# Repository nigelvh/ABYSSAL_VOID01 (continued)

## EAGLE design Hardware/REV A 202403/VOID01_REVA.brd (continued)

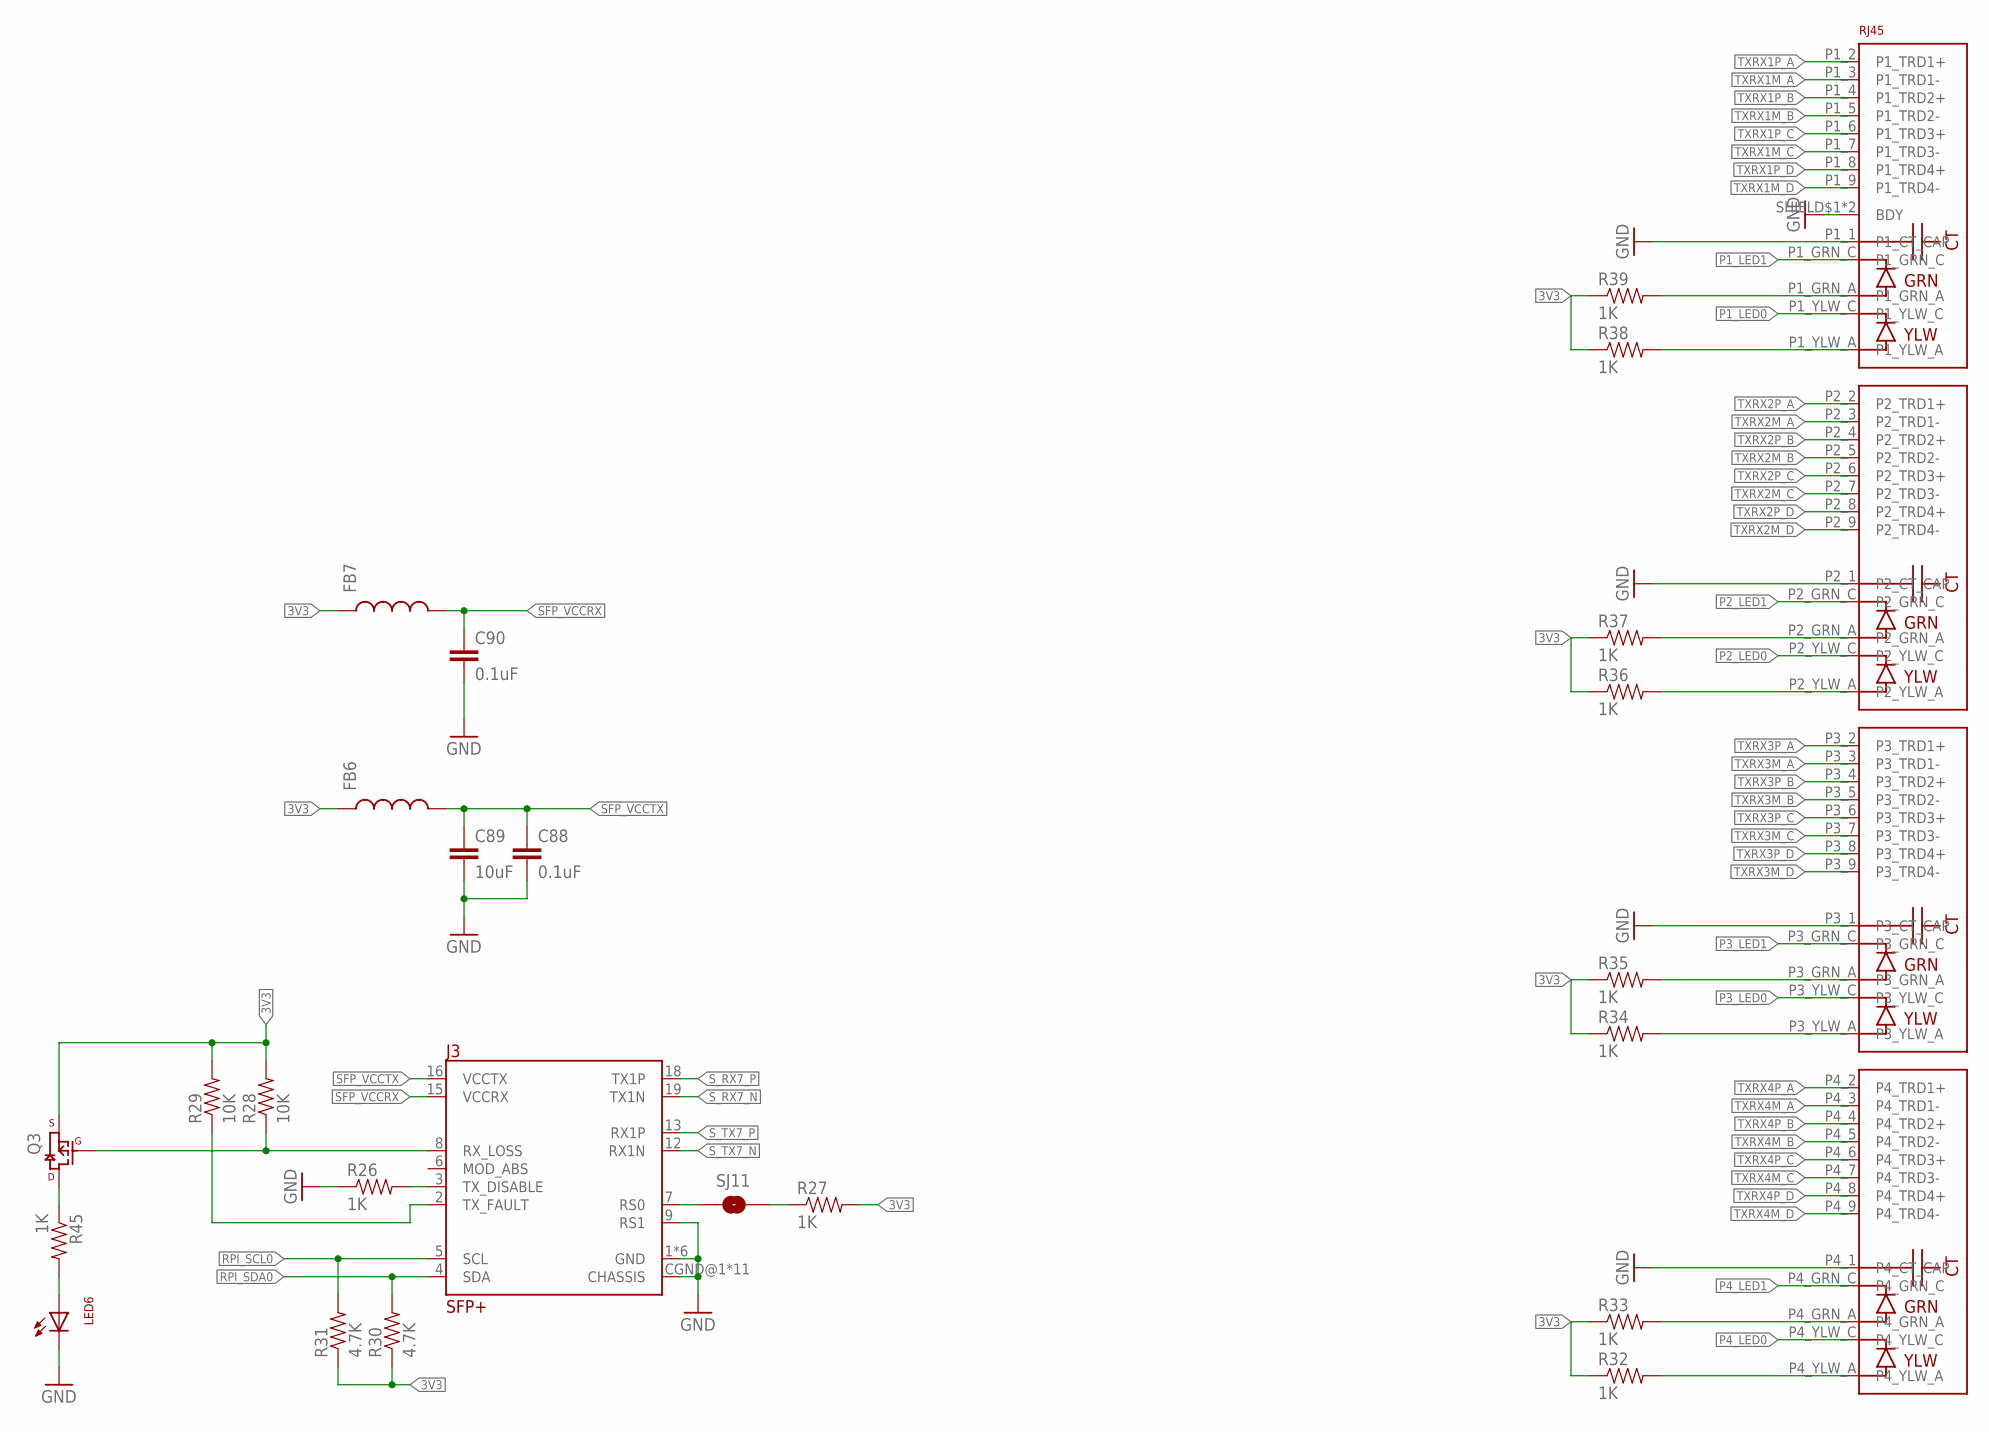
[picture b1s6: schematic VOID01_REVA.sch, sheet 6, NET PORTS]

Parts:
C88, C90: 0.1uF; 0402-CAP
C89: 10uF; 1206
FB6, FB7: INDUCTOR0805; 0805
J3: SFP; SFP_SOCKET_CAGE
J4: JXD0-4015NL
LED6: LED; LED_QBL7XX80D-MP4A
Q3: MOSFET_P_CHANNELAO3423; SOT-23
R26, R27: 1K; 0402-RES
R28: 10K; 0603-RES
R29: 10K; 0402-RES
R30, R31: 4.7K; 0402-RES
R32, R33, R34, R35, R36, R37, R38, R39, R45: 1K; 0603-RES
SJ11: SOLDERJUMPERNO; SJ_2S-NO

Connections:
3V3: FB6.1, FB7.1, Q3.2 (S), R27.2, R28.2, R29.2, R30.1, R31.1, R32.1, R33.1, R34.1, R35.1, R36.1, R37.1, R38.1, R39.1; also elsewhere on the board
GND: C88.2, C89.2, C90.2, J3.1 (GND), J3.9 (RS1), J3.10 (GND), J3.11 (GND), J3.14 (GND), J3.17 (GND), J3.20 (GND), J3.CGND@1 (CHASSIS), J3.CGND@6 (CHASSIS), J3.CGND@9 (CHASSIS), J3.CGND@11 (CHASSIS), J3.CGND@12 (CHASSIS), J3.CGND@13 (CHASSIS), J3.CGND@14 (CHASSIS), J3.CGND@15 (CHASSIS), J3.CGND@16 (CHASSIS), J3.CGND@19 (CHASSIS), J3.CGND@20 (CHASSIS), J4.P1_1 (P1_CT_CAP), J4.P2_1 (P2_CT_CAP), J4.P3_1 (P3_CT_CAP), J4.P4_1 (P4_CT_CAP), J4.SHIELD$1 (BDY), J4.SHIELD$5 (BDY), LED6.C, R26.1; also elsewhere on the board
unnamed: J4.P4_YLW_A, R32.2
unnamed: J4.P4_GRN_A, R33.2
unnamed: J4.P3_GRN_A, R35.2
unnamed: J4.P3_YLW_A, R34.2
unnamed: J4.P2_GRN_A, R37.2
unnamed: J4.P2_YLW_A, R36.2
unnamed: J4.P1_GRN_A, R39.2
unnamed: J4.P1_YLW_A, R38.2
unnamed: J3.3 (TX_DISABLE), R26.2
unnamed: J3.7 (RS0), SJ11.1
unnamed: R27.1, SJ11.2
unnamed: J3.8 (RX_LOSS), Q3.1 (G), R28.1
unnamed: J3.2 (TX_FAULT), R29.1
unnamed: LED6.A, R45.2
unnamed: Q3.3 (D), R45.1
P1_LED0: J4.P1_YLW_C; also elsewhere on the board
P1_LED1: J4.P1_GRN_C; also elsewhere on the board
P2_LED0: J4.P2_YLW_C; also elsewhere on the board
P2_LED1: J4.P2_GRN_C; also elsewhere on the board
P3_LED0: J4.P3_YLW_C; also elsewhere on the board
P3_LED1: J4.P3_GRN_C; also elsewhere on the board
P4_LED0: J4.P4_YLW_C; also elsewhere on the board
P4_LED1: J4.P4_GRN_C; also elsewhere on the board
RPI_SCL0: J3.5 (SCL), R31.2; also elsewhere on the board
RPI_SDA0: J3.4 (SDA), R30.2; also elsewhere on the board
SFP_VCCRX: C90.1, FB7.2, J3.15 (VCCRX)
SFP_VCCTX: C88.1, C89.1, FB6.2, J3.16 (VCCTX)
S_RX7_N: J3.19 (TX1N); also elsewhere on the board
S_RX7_P: J3.18 (TX1P); also elsewhere on the board
S_TX7_N: J3.12 (RX1N); also elsewhere on the board
S_TX7_P: J3.13 (RX1P); also elsewhere on the board
TXRX1M_A: J4.P1_3 (P1_TRD1-); also elsewhere on the board
TXRX1M_B: J4.P1_5 (P1_TRD2-); also elsewhere on the board
TXRX1M_C: J4.P1_7 (P1_TRD3-); also elsewhere on the board
TXRX1M_D: J4.P1_9 (P1_TRD4-); also elsewhere on the board
TXRX1P_A: J4.P1_2 (P1_TRD1+); also elsewhere on the board
TXRX1P_B: J4.P1_4 (P1_TRD2+); also elsewhere on the board
TXRX1P_C: J4.P1_6 (P1_TRD3+); also elsewhere on the board
TXRX1P_D: J4.P1_8 (P1_TRD4+); also elsewhere on the board
TXRX2M_A: J4.P2_3 (P2_TRD1-); also elsewhere on the board
TXRX2M_B: J4.P2_5 (P2_TRD2-); also elsewhere on the board
TXRX2M_C: J4.P2_7 (P2_TRD3-); also elsewhere on the board
TXRX2M_D: J4.P2_9 (P2_TRD4-); also elsewhere on the board
TXRX2P_A: J4.P2_2 (P2_TRD1+); also elsewhere on the board
TXRX2P_B: J4.P2_4 (P2_TRD2+); also elsewhere on the board
TXRX2P_C: J4.P2_6 (P2_TRD3+); also elsewhere on the board
TXRX2P_D: J4.P2_8 (P2_TRD4+); also elsewhere on the board
TXRX3M_A: J4.P3_3 (P3_TRD1-); also elsewhere on the board
TXRX3M_B: J4.P3_5 (P3_TRD2-); also elsewhere on the board
TXRX3M_C: J4.P3_7 (P3_TRD3-); also elsewhere on the board
TXRX3M_D: J4.P3_9 (P3_TRD4-); also elsewhere on the board
TXRX3P_A: J4.P3_2 (P3_TRD1+); also elsewhere on the board
TXRX3P_B: J4.P3_4 (P3_TRD2+); also elsewhere on the board
TXRX3P_C: J4.P3_6 (P3_TRD3+); also elsewhere on the board
TXRX3P_D: J4.P3_8 (P3_TRD4+); also elsewhere on the board
TXRX4M_A: J4.P4_3 (P4_TRD1-); also elsewhere on the board
TXRX4M_B: J4.P4_5 (P4_TRD2-); also elsewhere on the board
TXRX4M_C: J4.P4_7 (P4_TRD3-); also elsewhere on the board
TXRX4M_D: J4.P4_9 (P4_TRD4-); also elsewhere on the board
TXRX4P_A: J4.P4_2 (P4_TRD1+); also elsewhere on the board
TXRX4P_B: J4.P4_4 (P4_TRD2+); also elsewhere on the board
TXRX4P_C: J4.P4_6 (P4_TRD3+); also elsewhere on the board
TXRX4P_D: J4.P4_8 (P4_TRD4+); also elsewhere on the board

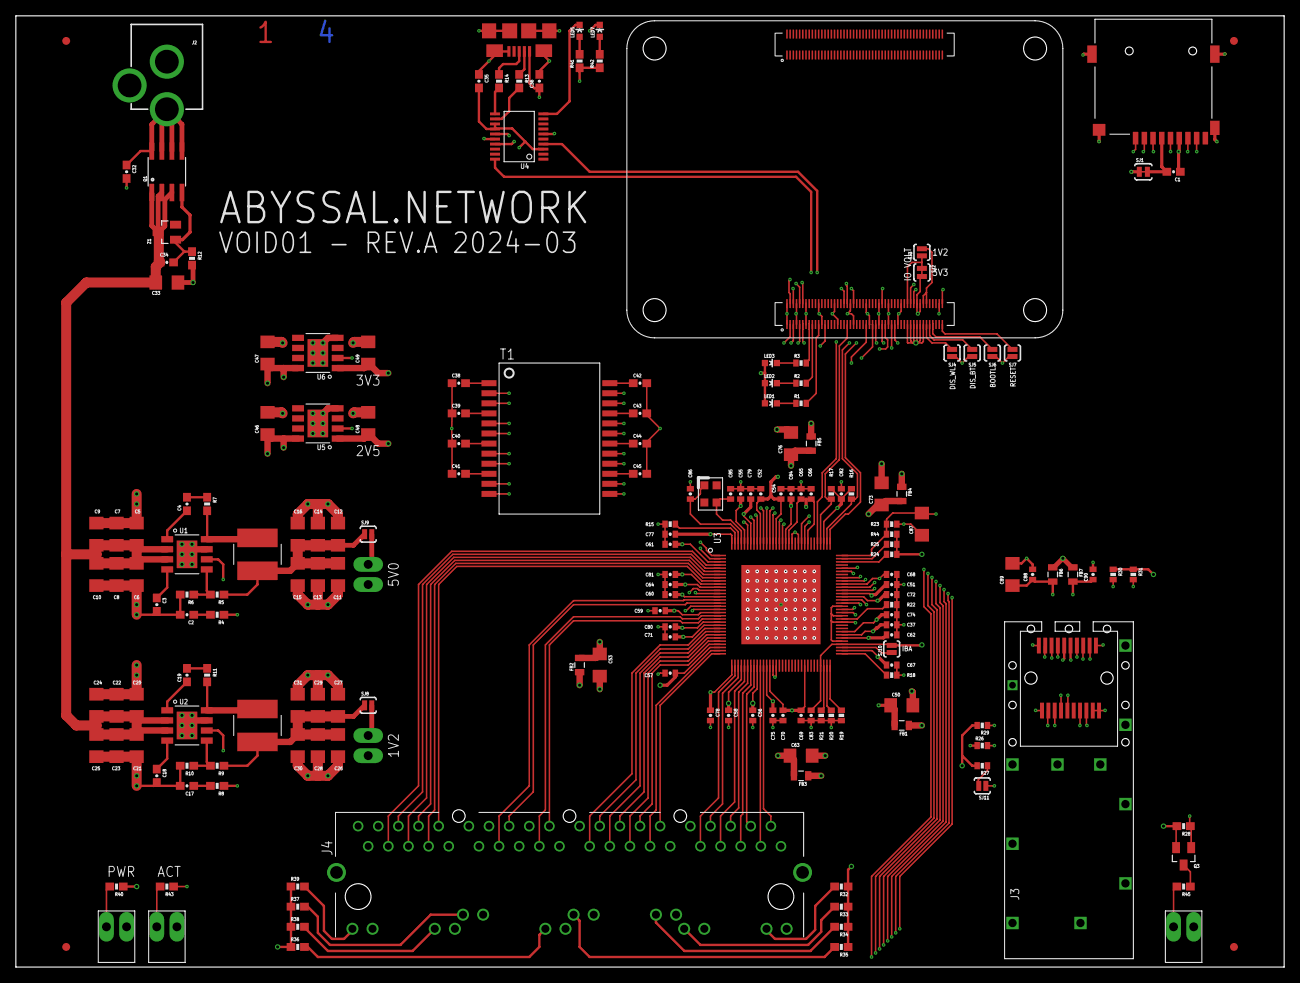
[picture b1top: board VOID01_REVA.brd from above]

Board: 4 copper layers, 160.0 x 120.0 mm, 186 parts (0 on the bottom side), 167 nets.

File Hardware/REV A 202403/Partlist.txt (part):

Partlist

Exported from CM4_SWITCH.brd at 3/10/24 19:35

EAGLE Version 7.7.0 Copyright (c) 1988-2016 CadSoft

Assembly variant: 

Part     Value                      Package             Library  Position (inch)       Orientation
C85      15pF                       0402-CAP            SparkFun (3.55 2.35)           R90
C86      15pF                       0402-CAP            SparkFun (3.35 2.35)           R270
C37      0.1uF                      0402-CAP            SparkFun (4.35 1.7)            R0
C51      0.1uF                      0402-CAP            SparkFun (4.35 1.9)            R0
C52      0.1uF                      0402-CAP            SparkFun (3.7 2.35)            R90
C54      0.1uF                      0402-CAP            SparkFun (3.8 2.35)            R90
C55      0.1uF                      0402-CAP            SparkFun (3.6 2.35)            R90
C56      0.1uF                      0402-CAP            SparkFun (3.66 1.25)           R270
C57      0.1uF                      0402-CAP            SparkFun (3.25 1.46)           R180
C58      0.1uF                      0402-CAP            SparkFun (3.54 1.25)           R270
C59      0.1uF                      0402-CAP            SparkFun (3.2 1.77)            R180
C60      0.1uF                      0402-CAP            SparkFun (3.25 1.85)           R180
C61      0.1uF                      0402-CAP            SparkFun (3.25 2.1)            R180
C62      0.1uF                      0402-CAP            SparkFun (4.35 1.65)           R0
C64      0.1uF                      0402-CAP            SparkFun (3.25 1.9)            R180
C65      0.1uF                      0402-CAP            SparkFun (3.9 2.35)            R90
C66      0.1uF                      0402-CAP            SparkFun (3.95 2.35)           R90
C67      0.1uF                      0402-CAP            SparkFun (4.35 1.5)            R0
C68      0.1uF                      0402-CAP            SparkFun (4.35 1.95)           R0
C69      0.1uF                      0402-CAP            SparkFun (3.9 1.25)            R270
C70      0.1uF                      0402-CAP            SparkFun (3.81 1.25)           R270
C71      0.1uF                      0402-CAP            SparkFun (3.25 1.64)           R180
C72      0.1uF                      0402-CAP            SparkFun (4.35 1.85)           R0
C74      0.1uF                      0402-CAP            SparkFun (4.35 1.75)           R0
C75      0.1uF                      0402-CAP            SparkFun (3.76 1.25)           R270
C77      0.1uF                      0402-CAP            SparkFun (3.25 2.15)           R180
C78      0.1uF                      0402-CAP            SparkFun (3.45 1.25)           R270
C79      0.1uF                      0402-CAP            SparkFun (3.65 2.35)           R90
C80      0.1uF                      0402-CAP            SparkFun (3.25 1.69)           R180
C81      0.1uF                      0402-CAP            SparkFun (3.25 1.95)           R180
C82      0.1uF                      0402-CAP            SparkFun (4.1 2.35)            R90
C83      0.1uF                      0402-CAP            SparkFun (3.95 1.25)           R270
C84      0.1uF                      0402-CAP            SparkFun (3.85 2.35)           R90
C88      0.1uF                      0402-CAP            SparkFun (5.05 1.95)           R90
C90      0.1uF                      0402-CAP            SparkFun (5.35 1.95)           R90

C2       2.7nF                      0603-CAP            SparkFun (0.85 1.75)           R180
C17      2.7nF                      0603-CAP            SparkFun (0.85 0.9)            R180
C3       0.1uF                      0603-CAP            SparkFun (0.7 1.8)             R270
C4       0.1uF                      0603-CAP            SparkFun (0.85 2.3)            R90
C18      0.1uF                      0603-CAP            SparkFun (0.7 0.95)            R270
C19      0.1uF                      0603-CAP            SparkFun (0.85 1.45)           R90
C32      0.1uF                      0603-CAP            SparkFun (0.55 3.95)           R270
C34      0.1uF                      0603-CAP            SparkFun (0.75 3.5)            R0
C35      0.1uF                      0603-CAP            SparkFun (2.3 4.4)             R270
C36      0.1uF                      0603-CAP            SparkFun (2.6 4.4)             R90
C38      0.1uF                      0603-CAP            SparkFun (2.2 2.9)             R0
C39      0.1uF                      0603-CAP            SparkFun (2.2 2.75)            R0
C40      0.1uF                      0603-CAP            SparkFun (2.2 2.6)             R0
C41      0.1uF                      0603-CAP            SparkFun (2.2 2.45)            R0
C42      0.1uF                      0603-CAP            SparkFun (3.1 2.9)             R0
C43      0.1uF                      0603-CAP            SparkFun (3.1 2.75)            R0
C44      0.1uF                      0603-CAP            SparkFun (3.1 2.6)             R0
C45      0.1uF                      0603-CAP            SparkFun (3.1 2.45)            R0
C1       0.1uF                      0603-CAP            SparkFun (5.75 3.95)           R180

C5       10uF                       1206                SparkFun (0.6 2.15)            R90
C6       10uF                       1206                SparkFun (0.6 1.95)            R270
C7       10uF                       1206                SparkFun (0.5 2.15)            R90
C8       10uF                       1206                SparkFun (0.5 1.95)            R270
C9       10uF                       1206                SparkFun (0.4 2.15)            R90
C10      10uF                       1206                SparkFun (0.4 1.95)            R270
C11      10uF                       1206                SparkFun (1.6 1.95)            R270
C12      10uF                       1206                SparkFun (1.6 2.15)            R90
C13      10uF                       1206                SparkFun (1.5 1.95)            R270
C14      10uF                       1206                SparkFun (1.5 2.15)            R90
C15      10uF                       1206                SparkFun (1.4 1.95)            R270
C16      10uF                       1206                SparkFun (1.4 2.15)            R90
C20      10uF                       1206                SparkFun (0.6 1.3)             R90
C21      10uF                       1206                SparkFun (0.6 1.1)             R270
C22      10uF                       1206                SparkFun (0.5 1.3)             R90
C23      10uF                       1206                SparkFun (0.5 1.1)             R270
C24      10uF                       1206                SparkFun (0.4 1.3)             R90
C25      10uF                       1206                SparkFun (0.4 1.1)             R270
C26      10uF                       1206                SparkFun (1.6 1.1)             R270
C27      10uF                       1206                SparkFun (1.6 1.3)             R90
C28      10uF                       1206                SparkFun (1.5 1.1)             R270
C29      10uF                       1206                SparkFun (1.5 1.3)             R90
C30      10uF                       1206                SparkFun (1.4 1.1)             R270
C31      10uF                       1206                SparkFun (1.4 1.3)             R90
C33      10uF                       1206                SparkFun (0.75 3.4)            R0
C46      10uF                       1206                SparkFun (1.25 2.7)            R90
C47      10uF                       1206                SparkFun (1.25 3.05)           R90
C48      10uF                       1206                SparkFun (1.75 2.7)            R90
C49      10uF                       1206                SparkFun (1.75 3.05)           R90
C50      10uF                       1206                SparkFun (4.4 1.3)             R0
C53      10uF                       1206                SparkFun (2.9 1.5)             R270
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
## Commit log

2024-03-19 Some initial folders/readme's.
2024-03-19 Added REV A hardware files.
